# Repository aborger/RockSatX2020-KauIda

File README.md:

# RockSatX2020-KauIda
Mission control and test software for use on the KauIda RockSat-X 2020 mission.

The software is split into two parts, the software for the arduino which runs the RF experiment, and the software for the Raspberry Pi in charge of the mission control.

# Arduino and RF experiment
The arduino (Pro Tinker) is connected to an Adafruit Bluefruit LE UART Friend, and an Adafruit BME680 sensor.
The connections are as follows:

| Pro Tinker | Bluefruit |    | Pro Tinker | BME680 |
|:----------:|:---------:|----|:----------:|:------:|
| Vin        | 5V        |    | Vin        | 5V     |
| GND        | GND       |    | GND        | GND    |
| 9          | RX0       |    | SCK        | A5     |
| 10         | TX1       |    | SDI        | A4     |
| 11         | CTS       |

The Pro Tinker is powered by a 5v button cell battery.

The Bluefruit's bluetooth services and characteristics must be setup before it is operational. The rockSat_Arduino_setup script can be ran to set it up. This script adds a service for the sensor data, and adds a characteristic for each individual sensor (RSSI, temperature, pressure, humidity, gas resistance, and altitude).

Once setup the rockSat_ArduinoV2 program can be uploaded and ran on the Arduino. This program waits for a connection and then repeatedly writes the sensor data to the bluetooth characteristics until powered off.

# Raspberry Pi and Mission Control

### Devices
The Raspberry Pi must control many different devices such as (The Gopro, RF receiver, Ricoh 360 degree camera, Scissor Boom, and door lock). These devices all inherit from the Device class which is found in ```RPiMaster/device.py``` The Device class demonstrates the structure each child class follows. The device class is as follows:

```python
class Device:
  def __init__(self, name):
		self.name = name
		print('Setting up ' + self.name + '...')

	def activate(self):
		print('Activating ' + self.name + '...')

	def deactivate(self):
		print('Deactivating ' + self.name + '...')

	def emergency(self):
		print(self.name + 'stopped immediately!')
 ```
 
As seen above each device has a name and three methods (activate, deactivate, and emergency). Each child may override these methods. These methods are the only public methods, they are the methods called in the Mission Control script. Some devices contain other private supporting methods.

### Detections
There are several signals that must be detected during the mission such as TE1 a timing signal from the rocket and a door shut signal from a limit switch. The Detect class waits for the low to high signal on a GPIO pin and has the ability to output a signal after the detection. The Detect class can be found in the ```RPIMaster/detect.py``` file.

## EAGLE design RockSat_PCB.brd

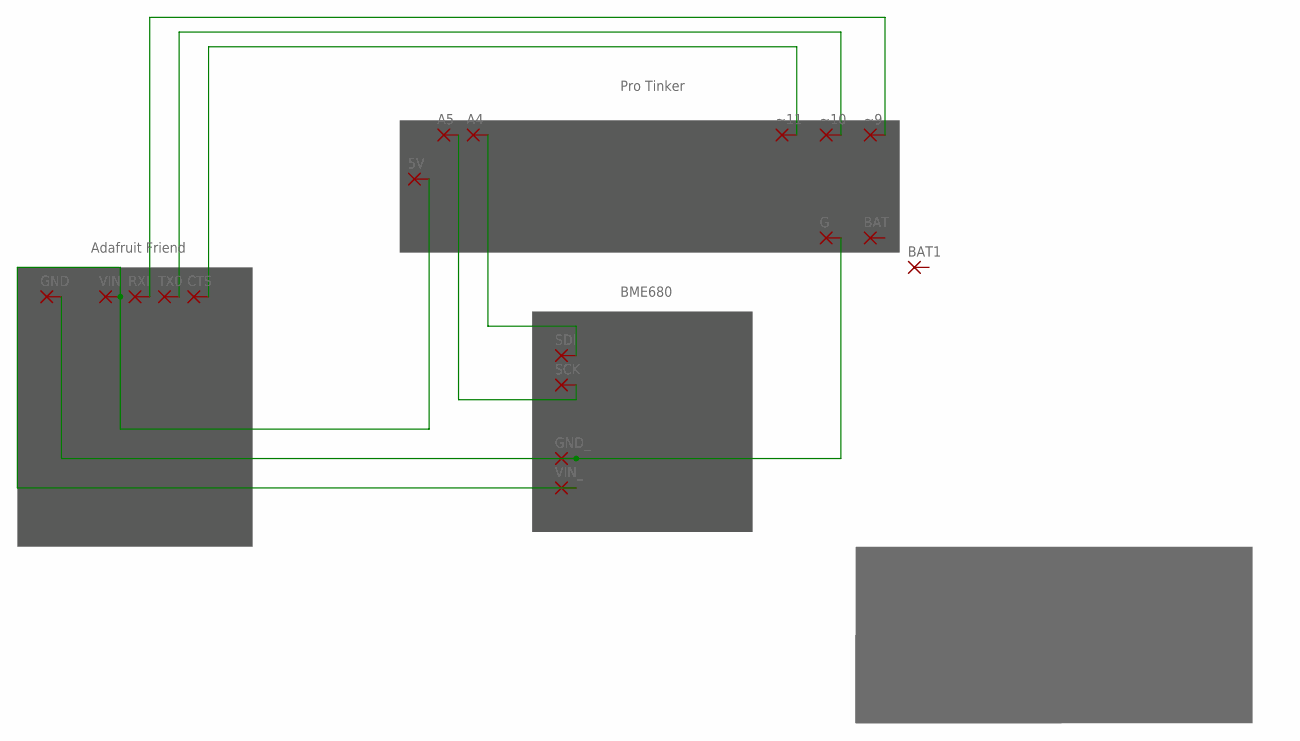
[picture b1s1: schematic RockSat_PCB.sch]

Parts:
5V: 1,6/0,9
A4, A5: 1,6/0,9
BAT, BAT1: 1,6/0,9
CTS: 1,6/0,9
G: 1,6/0,9
GND: 1,6/0,9
GND_: 1,6/0,9
RXI: 1,6/0,9
SCK: 1,6/0,9
SDI: 1,6/0,9
TX0: 1,6/0,9
VIN: 1,6/0,9
VIN_: 1,6/0,9
~9, ~10, ~11: 1,6/0,9

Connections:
unnamed: G.1, GND.1, GND_.1
unnamed: 5V.1, VIN.1, VIN_.1
unnamed: A5.1, SCK.1
unnamed: RXI.1, ~9.1
unnamed: TX0.1, ~10.1
unnamed: CTS.1, ~11.1
unnamed: A4.1, SDI.1

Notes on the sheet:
Pro Tinker
BME680
Adafruit Friend
NNU ROCKSAT: KUAIDA
R.F. Experiment PCB
2/1/2021
Drawing: N_Appleby
Sheet: 1/1
ISGC, ROCKSAT X

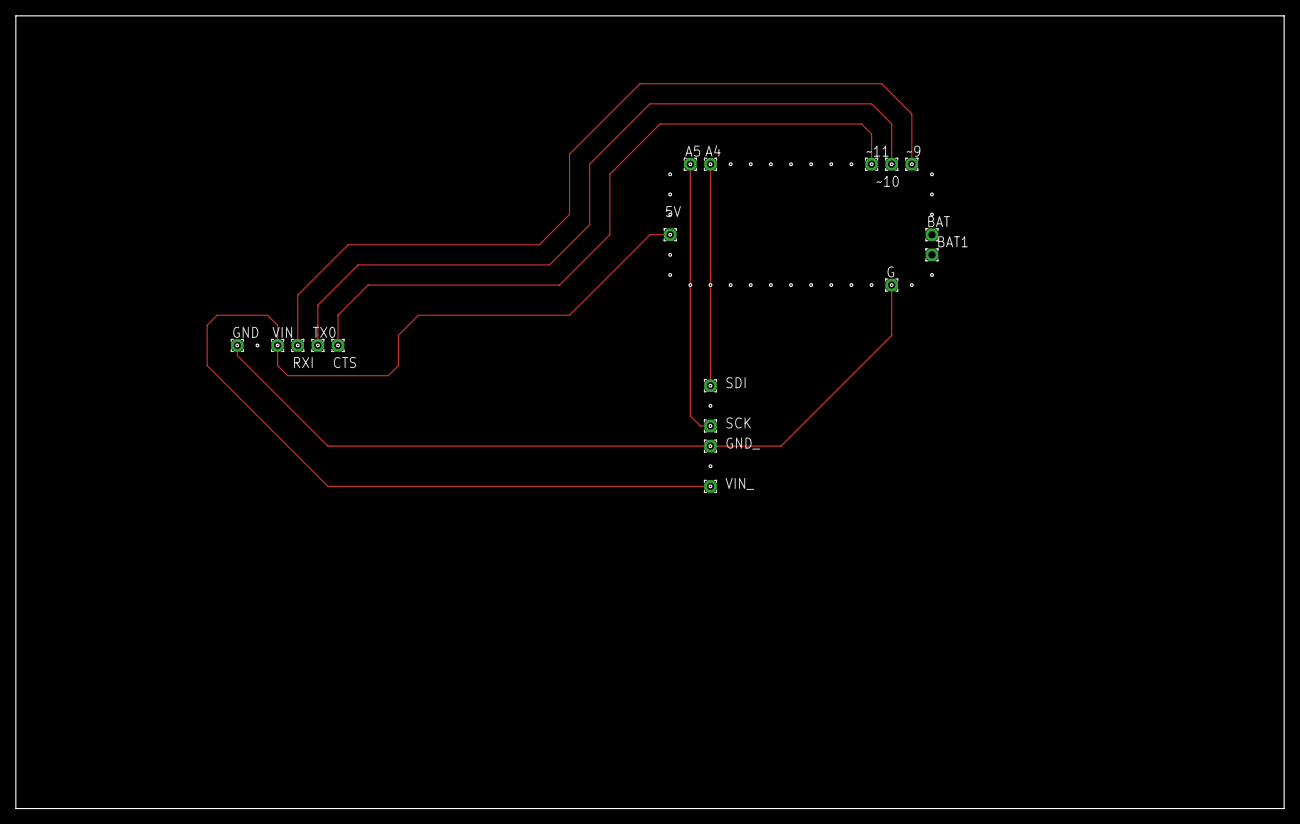
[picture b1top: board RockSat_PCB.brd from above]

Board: 2 copper layers, 160.0 x 100.0 mm, 18 parts (0 on the bottom side), 7 nets.

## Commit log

2020-10-23 organizing and starting master control
2020-10-26 added lock
2020-10-29 Master script
2020-10-29 rf almost fixed
2020-10-30 rf almost fixed (#1)
2020-11-04 rf system running
2020-11-04 rf works, master script halfway
2020-11-04 rf works, master script halfway (#2)
2020-11-04 Organized files
2020-11-12 added gopro and rf to master
2021-01-20 Rename Master.py to Mission_Control
2021-01-20 Rename Mission_Control to Mission_Control.py
2021-01-24 Master script updated
2021-01-24 started telemetry script
2021-01-28 Go pro works
2021-01-29 GoPro added to master script
2021-01-29 door shut limit switch added
2021-02-01 added eagle cad
2021-02-01 finished gopro, started thetaV
2021-02-02 ricoh added
2021-02-11 added turning bluetooth on
2021-02-16 added state machine mission control, updated telemetry
2021-02-16 added c wrapper to telem
2021-02-16 Update notes.txt
    Lower case 'L' not number '1'
2021-02-16 ricoh complete, gopro sometimes messes up, telemetry almost works
2021-04-01 testing cytron motor controller
2021-04-02 fixed goPro, fixed Limit Switch
2021-04-02 added cytron motor controller to Mission Control
2021-04-07 added servo test script
2021-04-15 fixed telemetry adding ricoh redundancy
2021-05-12 added theta function
2021-05-12 added wireless ricoh to device
2021-05-17 Create rpi_cam
2021-05-17 Update rpi_cam
2021-05-18 re-organizing the mission_control scripts
2021-05-19 finished new mission_control system
2021-05-20 limit doesnt work
2021-05-20 FMS should work
2021-05-21 organized bare_minimum
2021-05-21 organized more
2021-05-24 everything is function, but ricoh has issues
2021-05-26 full simulation ready
2021-05-27 telemetry fixed
2021-05-30 fixed a lot of stuff
2021-05-30 before rf change
2021-05-30 before recording ricoh in sections
2021-05-31 final testing
2021-06-01 30 min till shipping
